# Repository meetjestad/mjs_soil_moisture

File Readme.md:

MeetJeStad measurement setups from the soil moisture project
============================================================

This repository contains the arduino code and PCB design files for the MeetJeStad Soil Moisture and Green Roof measurement setups

Firmware is in the form of an Arduino Sketch, for more info on arduino and latest version see  https://www.arduino.cc

Electronics and PCB are designed in KiCad, which can be downloaded from https://kicad.org/

## Branches

- **master**: Contains the Firmware and design files of currently used the Meet Je Stad Soil Moisture measurement setup
- greenroof: Contains the Firmware of the currently used Meet Je Stad Green Roof measurement setup
- prototype_v3: Contains the Firmware and PCB design files for the Meet Je Stad Soil Moisture Prototype Version 3
- dendrometer: Contains the Firmware for the experimental dendrometer setup

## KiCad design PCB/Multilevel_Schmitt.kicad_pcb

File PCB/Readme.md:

Electronic schematic & PCB design
=================================

PCB was designed in KiCad version 5.1.6

List of components:

U1 = Microcontroller ATTINY84-20PU
U2 = Schmitt trigger SN74HC14
U3 = LDO MCP1700-250
U4 = Multiplexer 74HC5051
U5 = Multiplexer 74HC5051
U6 = Multiplexer 74HC5051
C1 = 100nF
C2 = 10uF
C3 = 39pF +/- 1%
C4 = 47pF
R1 = 3.3k
R2 = 3.3k
R3 = 1M +/- 0.1%
R4 = 5.6k
Thermistor_NTC = NTCLE305E4502SB

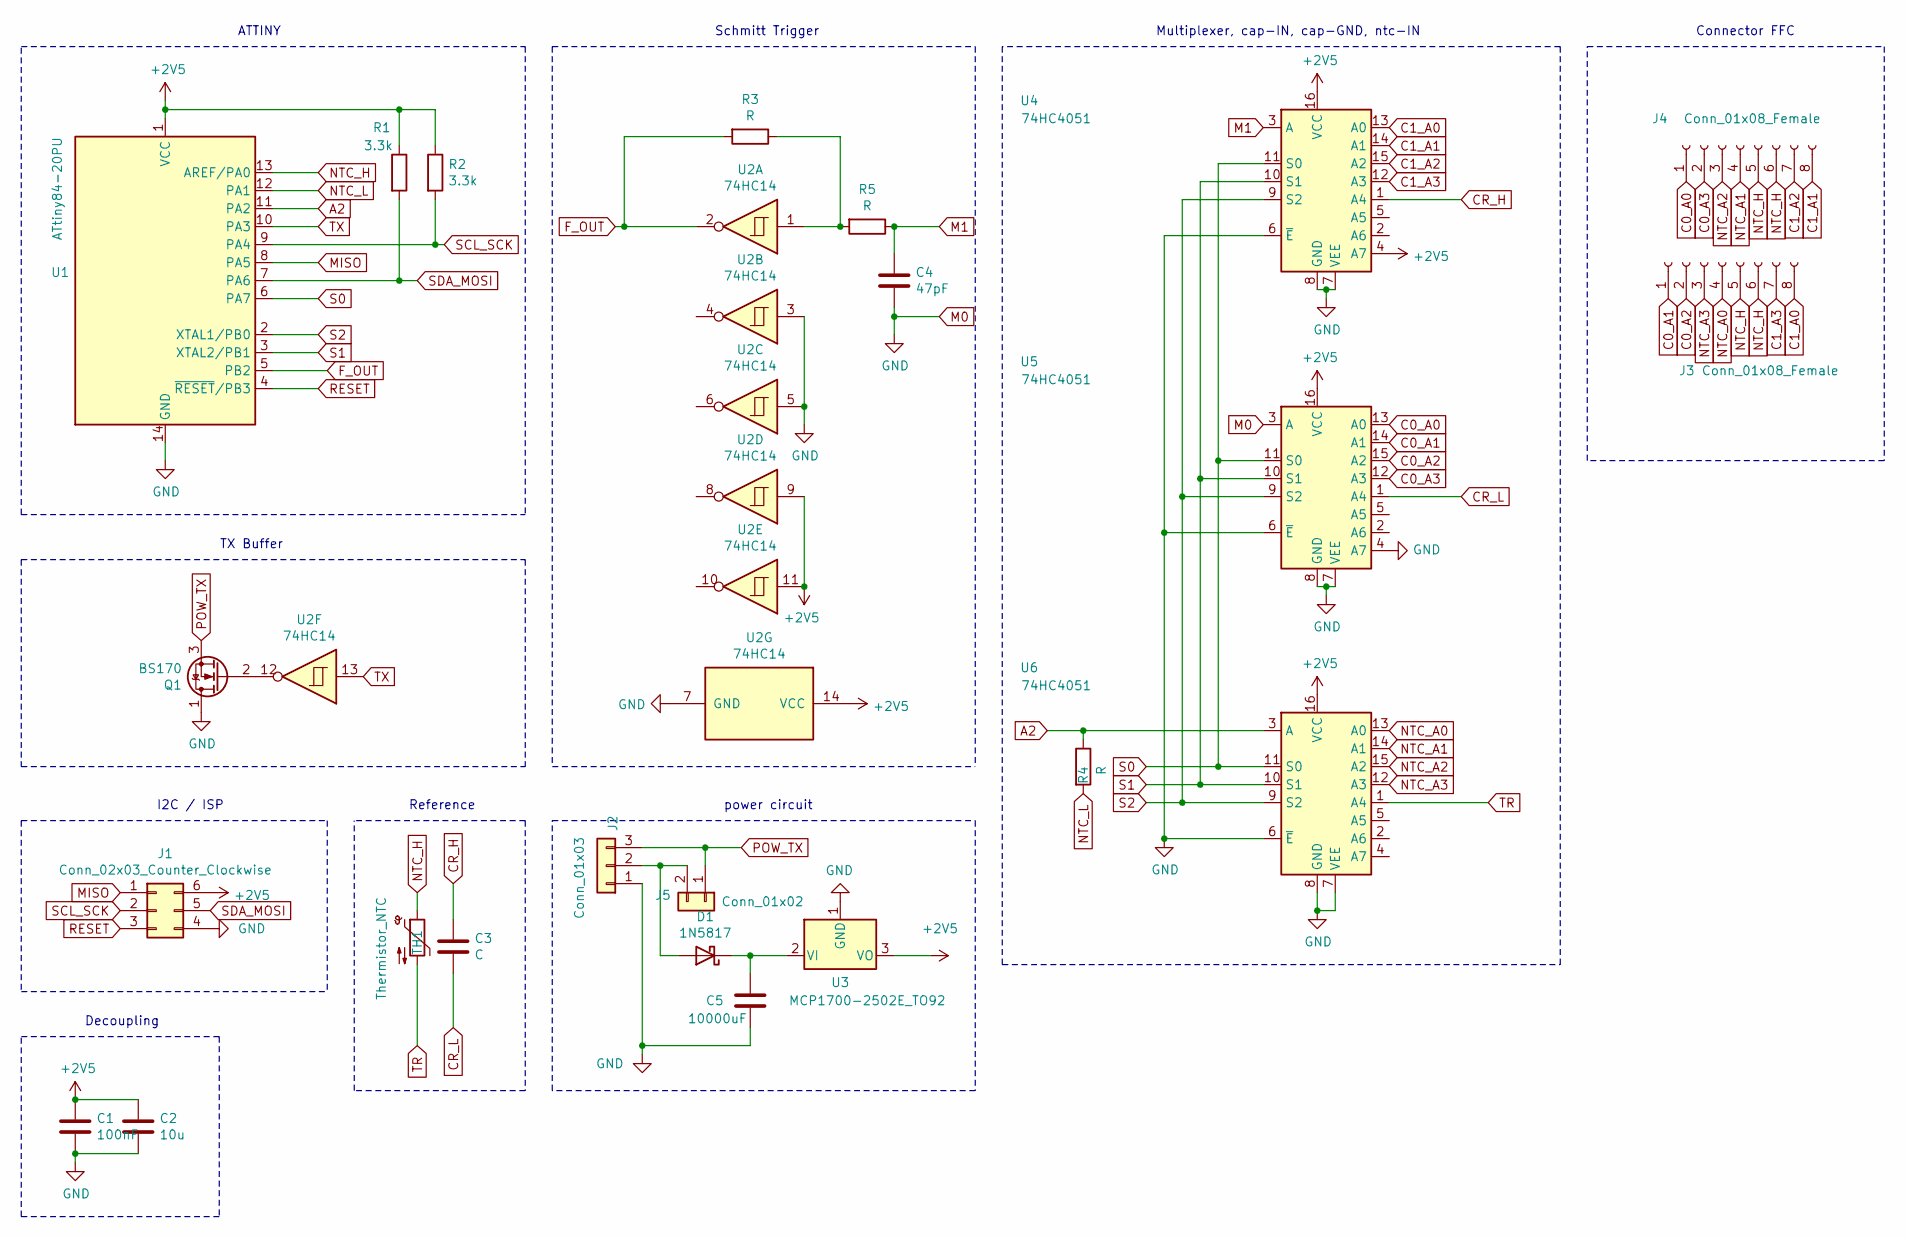
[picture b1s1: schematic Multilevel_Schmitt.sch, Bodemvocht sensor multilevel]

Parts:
C1: 100nF; C_Disc_D5.0mm_W2.5mm_P2.50mm
C2: 10u; CP_Radial_D5.0mm_P2.50mm
C3: C; R_Axial_DIN0207_L6.3mm_D2.5mm_P10.16mm_Horizontal
C4: 47pF; R_Axial_DIN0207_L6.3mm_D2.5mm_P10.16mm_Horizontal
C5: 10000uF; CP_Radial_D12.5mm_P5.00mm
D1: 1N5817; D_DO-41_SOD81_P10.16mm_Horizontal
J1: Conn_02x03_Counter_Clockwise; PinHeader_2x03_P2.54mm_Vertical
J2: Conn_01x03; PinHeader_1x03_P2.54mm_Vertical
J3, J4: Conn_01x08_Female; PinHeader_1x08_P1.00mm_Vertical
J5: Conn_01x02; PinHeader_1x02_P2.54mm_Vertical
Q1: BS170; TO-92_Inline_Wide
R1, R2: 3.3k; R_Axial_DIN0207_L6.3mm_D2.5mm_P10.16mm_Horizontal
R3, R4, R5: R; R_Axial_DIN0207_L6.3mm_D2.5mm_P10.16mm_Horizontal
TH1: Thermistor_NTC; C_Disc_D5.0mm_W2.5mm_P2.50mm
U1: ATtiny84-20PU; DIP-14_W7.62mm
U2: 74HC14; DIP-14_W7.62mm
U3: MCP1700-2502E_TO92; TO-92_Inline_Wide
U4, U5, U6: 74HC4051; DIP-16_W7.62mm

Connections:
+2V5: C1.1, C2.1, J1.6, R1.1, R2.1, U1.1 (VCC), U2.9, U2.11, U2.14 (VCC), U3.3 (VO), U4.4 (A7), U4.16 (VCC), U5.16 (VCC), U6.16 (VCC)
A2: R4.1, U1.11 (PA2), U6.3 (A)
C0_A0: J4.1, U5.13 (A0)
C0_A1: J3.1, U5.14 (A1)
C0_A2: J3.2, U5.15 (A2)
C0_A3: J4.2, U5.12 (A3)
C1_A0: J3.8, U4.13 (A0)
C1_A1: J4.8, U4.14 (A1)
C1_A2: J4.7, U4.15 (A2)
C1_A3: J3.7, U4.12 (A3)
CR_H: C3.1, U4.1 (A4)
CR_L: C3.2, U5.1 (A4)
F_OUT: R3.2, U1.5 (PB2), U2.2
M0: C1.2, C2.2, C4.2, C5.2, J1.4, J2.1, Q1.1 (D), U1.14 (GND), U2.3, U2.5, U2.7 (GND), U3.1 (GND), U4.6 (~E), U4.7 (VEE), U4.8 (GND), U5.3 (A), U5.4 (A7), U5.6 (~E), U5.7 (VEE), U5.8 (GND), U6.6 (~E), U6.7 (VEE), U6.8 (GND)
M1: C4.1, R5.1, U4.3 (A)
MISO: J1.1, U1.8 (PA5)
NTC_A0: J3.4, U6.13 (A0)
NTC_A1: J4.4, U6.14 (A1)
NTC_A2: J4.3, U6.15 (A2)
NTC_A3: J3.3, U6.12 (A3)
NTC_H: J3.5, J3.6, J4.5, J4.6, TH1.1, U1.13 (AREF/PA0)
NTC_L: R4.2, U1.12 (PA1)
unnamed: C5.1, D1.1 (K), U3.2 (VI)
unnamed: D1.2 (A), J2.2, J5.2
unnamed: Q1.2 (G), U2.12
unnamed: R3.1, R5.2, U2.1
POW_TX: J2.3, J5.1, Q1.3 (S)
RESET: J1.3, U1.4 (~RESET~/PB3)
S0: U1.6 (PA7), U4.11 (S0), U5.11 (S0), U6.11 (S0)
S1: U1.3 (XTAL2/PB1), U4.10 (S1), U5.10 (S1), U6.10 (S1)
S2: U1.2 (XTAL1/PB0), U4.9 (S2), U5.9 (S2), U6.9 (S2)
SCL_SCK: J1.2, R2.2, U1.9 (PA4)
SDA_MOSI: J1.5, R1.2, U1.7 (PA6)
TR: TH1.2, U6.1 (A4)
TX: U1.10 (PA3), U2.13

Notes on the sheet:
Schmitt Trigger
ATTINY
Multiplexer, cap-IN, cap-GND, ntc-IN
Reference
Decoupling
I2C / ISP
power circuit
TX Buffer
Connector FFC

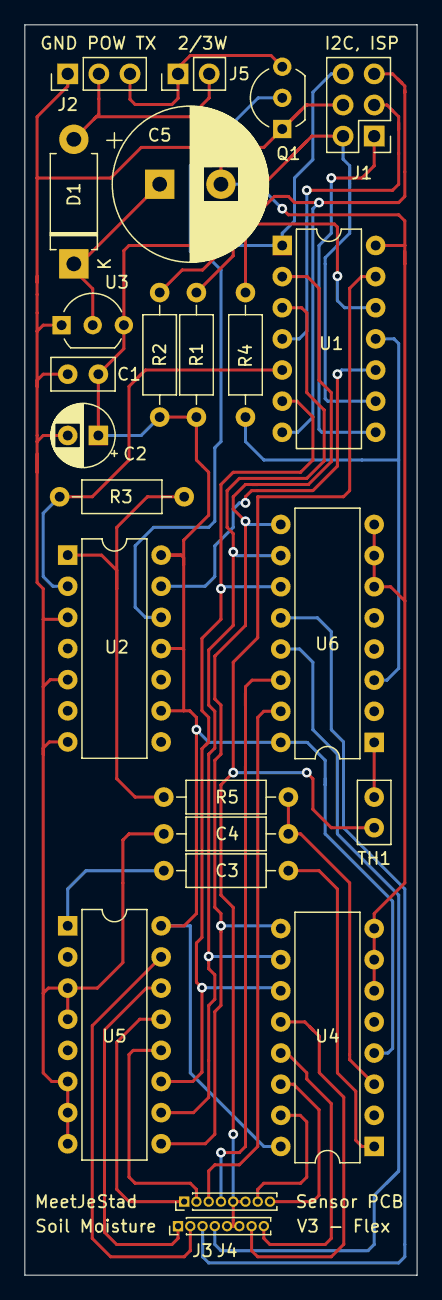
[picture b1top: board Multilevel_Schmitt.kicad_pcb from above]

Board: 2 copper layers, 32.0 x 102.0 mm, 24 parts (0 on the bottom side), 35 nets.

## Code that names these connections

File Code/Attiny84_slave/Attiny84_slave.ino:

//before uploading set the arduino as ISP, using the example sketch, ArduinoISP

// Code for the ATtiny84
// Board = ATtiny84
//Processor = Attiny84
//Clock speed = 8mhz
//Programmer = Arduino as ISP

#define I2C_SLAVE_ADDRESS 0x4 // Address of the slave
 
#include <TinyWireS.h>
#include <avr/io.h>
#include <avr/interrupt.h>

//measurement 
const int samples=50;
const int num=6; //4 levels and 2xreference
unsigned long interval = 10000;
float C_raw_freq[samples];
float k = 1;
float R=996000; //Mohm

//for the I2C data transfer
uint8_t reg=0;

//for interrupt
volatile long pulseCount; 
unsigned long lastReportTime;
unsigned long true_interval;
volatile boolean pulseOn; 

//Data storage and settings for each level
struct level{
  int S0;
  int S1;
  int S2;
  int E;
};

struct level L[num];

union fl{
  float F;
  unsigned char b[4];
};

fl av;
fl st;

union t{
  uint16_t raw;
  unsigned char b[2];
} T;

//pin declaration
int S0=7;
int S1=9;
int S2=10;
int E=3;
int NTC_L=1;
int NTC_H=0;
int NTC_I=A2;
int F_OUT=8;

//multiplexer settings
void setMult(){
  L[0].S0=0;
  L[0].S1=0;
  L[0].S2=0;
  L[0].E=1;
  
  L[1].S0=0;
  L[1].S1=1;
  L[1].S2=0;
  L[1].E=0;
  
  L[2].S0=1;
  L[2].S1=0;
  L[2].S2=0;
  L[2].E=0;
  
  L[3].S0=0;
  L[3].S1=0;
  L[3].S2=0;
  L[3].E=0;
  
  L[4].S0=1;
  L[4].S1=1;
  L[4].S2=0;
  L[4].E=0;

  L[5].S0=0;
  L[5].S1=0;
  L[5].S2=1;
  L[5].E=0;
}

//interrupt function
ISR(INT0_vect){
  if(pulseOn){
    pulseCount++;
  }
} 

//averaging function
float array_mean(float arr[samples]){
  float sum=0;
  float mean;
  for(int i=0;i<samples;i++){
    sum+=arr[i];
  }
  
  mean=sum/float(samples);
  return mean;
}

//standard deviation
float array_stdev(float arr[samples]){
  float mean=array_mean(arr);
  float var=0;
  float st;
  
  for(int i=0;i<samples;i++){
    var+=pow((float(arr[i])-mean),2);
  }
  
  st=pow((var/float(samples)),0.5);
  return st;
}

uint16_t NTC_temp(int tsample){

  //set to output
  pinMode(NTC_L, OUTPUT); 
  pinMode(NTC_H, OUTPUT); 
  delay(100);
  digitalWrite(NTC_L, LOW);
  digitalWrite(NTC_H, HIGH);
  delay(100);

  //measurement
  int T_sum=0;
  int t=0;
  while(t<tsample){
    T_sum+=analogRead(NTC_I);
    t=t+1; 
  }

  pinMode(NTC_L, INPUT); // floating
  pinMode(NTC_H, INPUT); // floating

  return T_sum/t;  
  
}

//measurement loop
void measure_loop(){
  int c=0;
  
  //set the multiplexer
  digitalWrite(S0,L[reg].S0);
  digitalWrite(S1,L[reg].S1);
  digitalWrite(S2,L[reg].S2);
  digitalWrite(E,L[reg].E);

  //Switching delay
  delay(100);

  //start the measurement
  pulseCount = 0;
  lastReportTime=micros();
  pulseOn=true;

  while(c<samples){

    //check if interval has passed
    if (micros()-lastReportTime >= interval) {

      true_interval=micros() - lastReportTime;
      
      // record the amount of pulses
      pulseOn=false;
      C_raw_freq[c]=1000000*pulseCount/true_interval;
      c++;

      //restart
      lastReportTime=micros();
      pulseCount = 0;
      pulseOn=true;
    }
  }

  //calcultae result
  pulseOn=false;

  //calculate and store frequency data 
  av.F=array_mean(C_raw_freq);
  st.F=array_stdev(C_raw_freq);
  T.raw=NTC_temp(10); //10=number of samples

  //reset the array
  for(int i=0; i<samples;i++){
    C_raw_freq[i]=0;
  }
}

void setup(){

  //Set the pins
  pinMode(S0, OUTPUT);
  pinMode(S1, OUTPUT);
  pinMode(S2, OUTPUT);
  pinMode(E, OUTPUT);

  pinMode(NTC_L, INPUT); // floating
  pinMode(NTC_H, INPUT); // floating
  pinMode(NTC_I, INPUT); // actual input

  digitalWrite(S0,LOW);
  digitalWrite(S1,LOW);
  digitalWrite(S2,LOW);
  digitalWrite(E,LOW);

  //set the multiplexer values
  setMult();
    
  // start I2C
  TinyWireS.begin(I2C_SLAVE_ADDRESS); // join i2c network
  TinyWireS.onRequest(requestEvent);
  TinyWireS.onReceive(recieveEvent);

  //do not start counting pulses yet
  pulseOn=false;


  //attach interrupt //Taken from https://forum.arduino.cc/index.php?topic=427955.0
  // Interrupt on INT0 working, on PCIE1 interferes with SDA and SCL
  PCMSK1 |= (1 << PCINT10); // pin 8 or PCINT10 as poin change interrupt
  //GIFR |= (1 << PCIF1);  //clear any outstanding interrupts   
  GIMSK |= (1 << INT0); // enable external pin change interrupt
  MCUCR |= (1<<ISC01)|(1<<ISC00); // set fire condition: rising edge
  pinMode(8, INPUT_PULLUP); //stabalize the pin
  sei();
 
}

void loop(){
    // This needs to be here
    TinyWireS_stop_check();
}

// Gets called when the ATtiny receives an i2c request
void requestEvent(){
    
    //send the register
    TinyWireS.send(reg);
    TinyWireS.send(av.b[0]);
    TinyWireS.send(av.b[1]);
    TinyWireS.send(av.b[2]);
    TinyWireS.send(av.b[3]);
    TinyWireS.send(st.b[0]);
    TinyWireS.send(st.b[1]);
    TinyWireS.send(st.b[2]);
    TinyWireS.send(st.b[3]);
    TinyWireS.send(T.b[0]);
    TinyWireS.send(T.b[1]);
    
}

void recieveEvent(){
  
  while(TinyWireS.available()){
    reg=TinyWireS.receive();
  }

  //perform measurement for this level
  measure_loop();
  
}

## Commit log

2020-07-15 name change
2020-07-15 readme files added
2020-07-15 Casing added
2020-10-25 Split firmware into production and diagnostics
2020-10-25 1s Wire Timeout included
2020-10-27 changed debug output and measurement interval to 30 min
2020-11-09 load cell sketch
2020-11-09 deleted diagnose sketches
2020-11-09 changed author information and measurement interval
2020-11-09 Updates PCB design files, removed casing files and updates readme files
2020-11-09 updates Readme
2021-01-07 latest changes to PCB design
2021-01-07 code authorship added
2021-01-07 Attiny firmware adjusted for PCB changes
2021-02-17 added pcb-bak just to be sure
2021-02-19 lastest version of slave firmware
2021-03-04 start with flex version
2021-03-04 changes in schematic
2021-03-11 changes in firmware slave & mjs master
2021-03-15 PCB version 3
2021-04-16 new pcb
2021-04-16 firmware update
2021-04-16 large cap holes
2021-11-07 Update Readme.md
    https://forum.kicad.info/t/warning-avoid-all-links-to-kicad-pcb-org-use-kicad-org/31521
2021-12-21 first commit greenroof
2021-12-21 last changes to master
2021-12-21 last change before merge
2022-03-03 Green roofs latest version
2022-03-03 cleaned up branch green roof
2022-03-03 Latest version with analog soil moisture sensors
2022-03-03 cleaned up master branch
2022-03-30 The sketch now also works with the original AVR board and can be ran alongside particle matter measurements
2022-06-29 savedall code to master
2022-06-29 Changed reference resistance value
2022-07-10 SDC30 turned off
2022-12-20 cleaned up master branche
2022-12-20 moved Dendrometer code to seperate branch
2022-12-20 cleaned up branche dendrometer
2022-12-20 Added design files for connector / soldering aid
